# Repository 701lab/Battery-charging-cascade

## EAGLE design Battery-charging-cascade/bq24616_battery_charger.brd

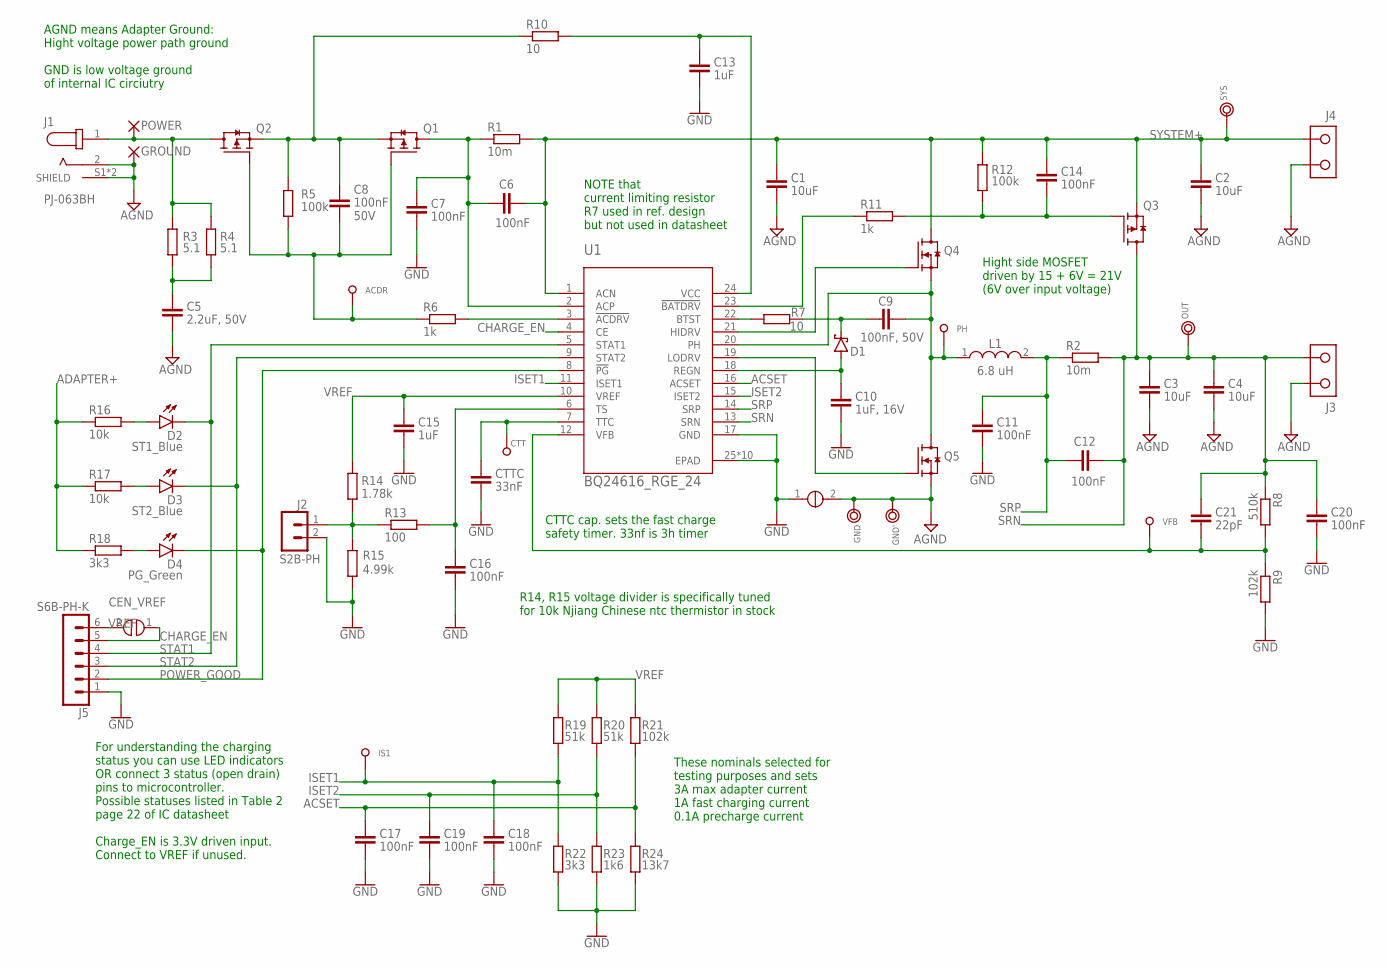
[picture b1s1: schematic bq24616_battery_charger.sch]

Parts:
ACDR: TEST_PAD-[1.27MM]; TP1.27MM
C1, C2, C3, C4: 10uF; C1206
C5: 2.2uF, 50V; C0805
C6, C7, C8, C11, C12, C14, C16, C17, C18, C19, C20: 100nF; C0603
C9: 100nF, 50V; C0603
C10: 1uF, 16V; C0603
C13, C15: 1uF; C0603
C21: 22pF; C0603
CEN_VREF: SOLDER_BRIDGE
CTT: TEST_PAD-[1.27MM]; TP1.27MM
CTTC: 33nF; C0603
D1: SOD523-SCHOTTKY; SOD523
D2: ST1_Blue; LED-0805
D3: ST2_Blue; LED-0805
D4: PG_Green; LED-0805
GND: TEST_RING
GND': TEST_RING
GROUND: WIRE_TO_BOARD_2,54/1,1; 2,54/1,1
IS1: TEST_PAD-[1.27MM]; TP1.27MM
J1: PJ-063BH; CUI_PJ-063BH
J2: S2B-PH; S2B-PH-K
J3, J4: DG301-2P"; DG301-2P
J5: S6B-PH-K
L1: 6.8 uH; SMD-0630
OUT: TEST_RING
PH: TEST_PAD-[1.27MM]; TP1.27MM
POWER: WIRE_TO_BOARD_2,54/1,1; 2,54/1,1
Q1, Q2, Q3: SI7121DN-T1-GE3; VISHAY_SI7121DN-T1-GE3
Q4, Q5: SON5X6_MOSFET; SON5X6
R1, R2: 10m; CS_R0805
R3, R4: 5.1; R1206
R5, R12: 100k; R0603
R6, R11: 1k; R0603
R7: 10; R0603
R8: 510k; R0603
R9, R21: 102k; R0603
R10: 10; R1206
R13: 100; R0603
R14: 1.78k; R0603
R15: 4.99k; R0603
R16, R17: 10k; R0603
R18, R22: 3k3; R0603
R19, R20: 51k; R0603
R23: 1k6; R0603
R24: 13k7; R0603
SB2: SHORT
SYS: TEST_RING
U1: BQ24616_RGE_24; RGE24_2P45X2P45
VFB: TEST_PAD-[1.27MM]; TP1.27MM

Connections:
ACDRV: R6.2, U1.3 (!ACDRV)
ACP: C6.1, C7.1, Q1.5 (D), Q1.6 (D), Q1.7 (D), Q1.8 (D), Q1.9 (D), R1.1, U1.2 (ACP)
ACSET: C17.1, R21.1, R24.2, U1.16 (ACSET)
ADAPTER+: J1.1, POWER.1, Q2.5 (D), Q2.6 (D), Q2.7 (D), Q2.8 (D), Q2.9 (D), R3.2, R4.2, R16.1, R17.1, R18.1
AGND: C1.2, C2.2, C3.2, C4.2, C5.2, GND.1, GND'.1, GROUND.1, J1.2, J1.S1 (SHIELD), J1.S2 (SHIELD), J3.1, J4.2, Q5.1 (S), Q5.2 (S), Q5.3 (S), SB2.2
BATDRV: R11.1, U1.23 (!BATDRV)
BTST: R7.1, U1.22 (BTST)
BTST1: C9.1, D1.C, R7.2
CHARGE_EN: CEN_VREF.1, J5.5, U1.4 (CE)
GATE: ACDR.1, C8.2, Q1.4 (G), Q2.4 (G), R5.2, R6.1
GND: C7.2, C10.2, C11.2, C13.2, C15.2, C16.2, C17.2, C18.2, C19.2, C20.2, CTTC.2, J2.2, J5.1, R9.2, R15.2, R22.1, R23.1, R24.1, SB2.1, U1.17 (GND), U1.25 (EPAD), U1.V (EPAD), U1.V_1 (EPAD), U1.V_2 (EPAD), U1.V_3 (EPAD), U1.V_4 (EPAD), U1.V_5 (EPAD), U1.V_6 (EPAD), U1.V_7 (EPAD), U1.V_8 (EPAD)
HIDRV: Q4.4 (G), U1.21 (HIDRV)
ISET1: C18.1, IS1.1, R19.1, R22.2, U1.11 (ISET1)
ISET2: C19.1, R20.1, R23.2, U1.15 (ISET2)
LODRV: Q5.4 (G), U1.19 (LODRV)
unnamed: C5.1, R3.1, R4.1
unnamed: C14.2, Q3.4 (G), R11.2, R12.2
unnamed: J2.1, R13.1, R14.2, R15.1
unnamed: D2.+ (A), R16.2
unnamed: D3.+ (A), R17.2
unnamed: D4.+ (A), R18.2
PH: C9.2, L1.1, PH.1, Q4.1 (S), Q4.2 (S), Q4.3 (S), Q5.5 (D), Q5.6 (D), Q5.7 (D), Q5.8 (D), Q5.9 (D), U1.20 (PH)
POWER_GOOD: D4.- (C), J5.2, U1.8 (!PG)
REGN: C10.1, D1.A, U1.18 (REGN)
SRN: C3.1, C4.1, C12.2, C20.1, C21.1, J3.2, OUT.1, Q3.5 (D), Q3.6 (D), Q3.7 (D), Q3.8 (D), Q3.9 (D), R2.2, R8.1, U1.13 (SRN)
SRP: C11.1, C12.1, L1.2, R2.1, U1.14 (SRP)
STAT1: D2.- (C), J5.4, U1.5 (STAT1)
STAT2: D3.- (C), J5.3, U1.9 (STAT2)
SYSTEM+: C1.1, C2.1, C6.2, C14.1, J4.1, Q3.1 (S), Q3.2 (S), Q3.3 (S), Q4.5 (D), Q4.6 (D), Q4.7 (D), Q4.8 (D), Q4.9 (D), R1.2, R12.1, SYS.1, U1.1 (ACN)
TCC: CTT.1, CTTC.1, U1.7 (TTC)
TS: C16.1, R13.2, U1.6 (TS)
VCC: C13.1, R10.2, U1.24 (VCC)
VCC1: C8.1, Q1.1 (S), Q1.2 (S), Q1.3 (S), Q2.1 (S), Q2.2 (S), Q2.3 (S), R5.1, R10.1
VFB: C21.2, R8.2, R9.1, U1.12 (VFB), VFB.1
VREF: C15.1, CEN_VREF.2, J5.6, R14.1, R19.2, R20.2, R21.2, U1.10 (VREF)

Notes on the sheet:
AGND means Adapter Ground: Hight voltage power path ground GND is low voltage ground of internal IC circiutry
NOTE that current limiting resistor R7 used in ref. design but not used in datasheet
Hight side MOSFET driven by 15 + 6V = 21V (6V over input voltage)
CTTC cap. sets the fast charge safety timer. 33nf is 3h timer
For understanding the charging status you can use LED indicators OR connect 3 status (open drain) pins to microcontroller. Possible statuses listed in Table 2 page 22 of IC datasheet Charge_EN is 3.3V driven input. Connect to VREF if unused.
50V
These nominals selected for testing purposes and sets 3A max adapter current 1A fast charging current 0.1A precharge current
R14, R15 voltage divider is specifically tuned for 10k Njiang Chinese ntc thermistor in stock

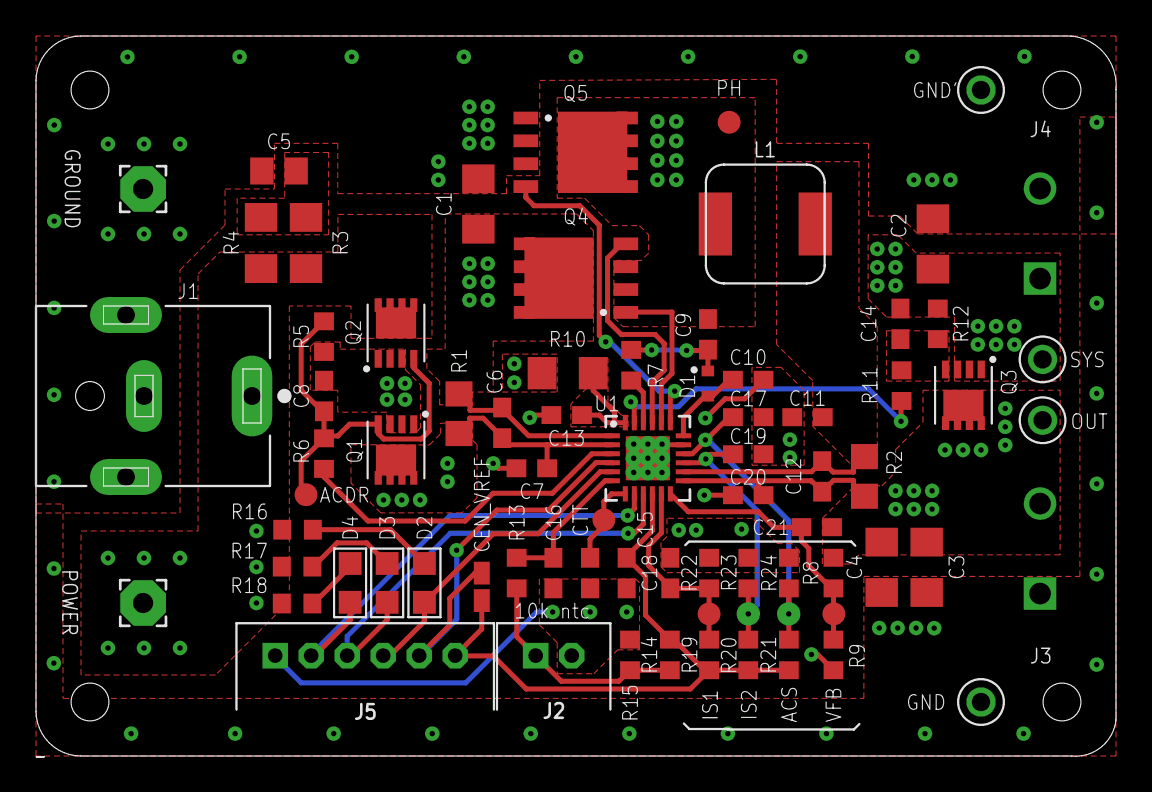
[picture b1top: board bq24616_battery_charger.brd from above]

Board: 2 copper layers, 60.0 x 40.0 mm, 75 parts (1 on the bottom side), 35 nets.

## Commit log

2020-02-16 schematic witout values
2020-02-22 schematic for review
2020-02-24 final routing for rewive
2020-02-25 ready to manufacturing
2020-05-03 assemble draw

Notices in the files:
parts and their libraries:
con-jst-ph: Copyright (C) 2016, Bob Starr
